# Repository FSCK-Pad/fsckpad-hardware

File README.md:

# FSCKPad Hardware

## Openhardware game controller/emulation handheld

---

## Installation

`cd fsckpad-hardware`  
`make install-dev`  

## Usage

`$ make help`  
`$ make build`  

---
Created from device-cookiecutter, https://github.com/crashfrog/device-cookiecutter

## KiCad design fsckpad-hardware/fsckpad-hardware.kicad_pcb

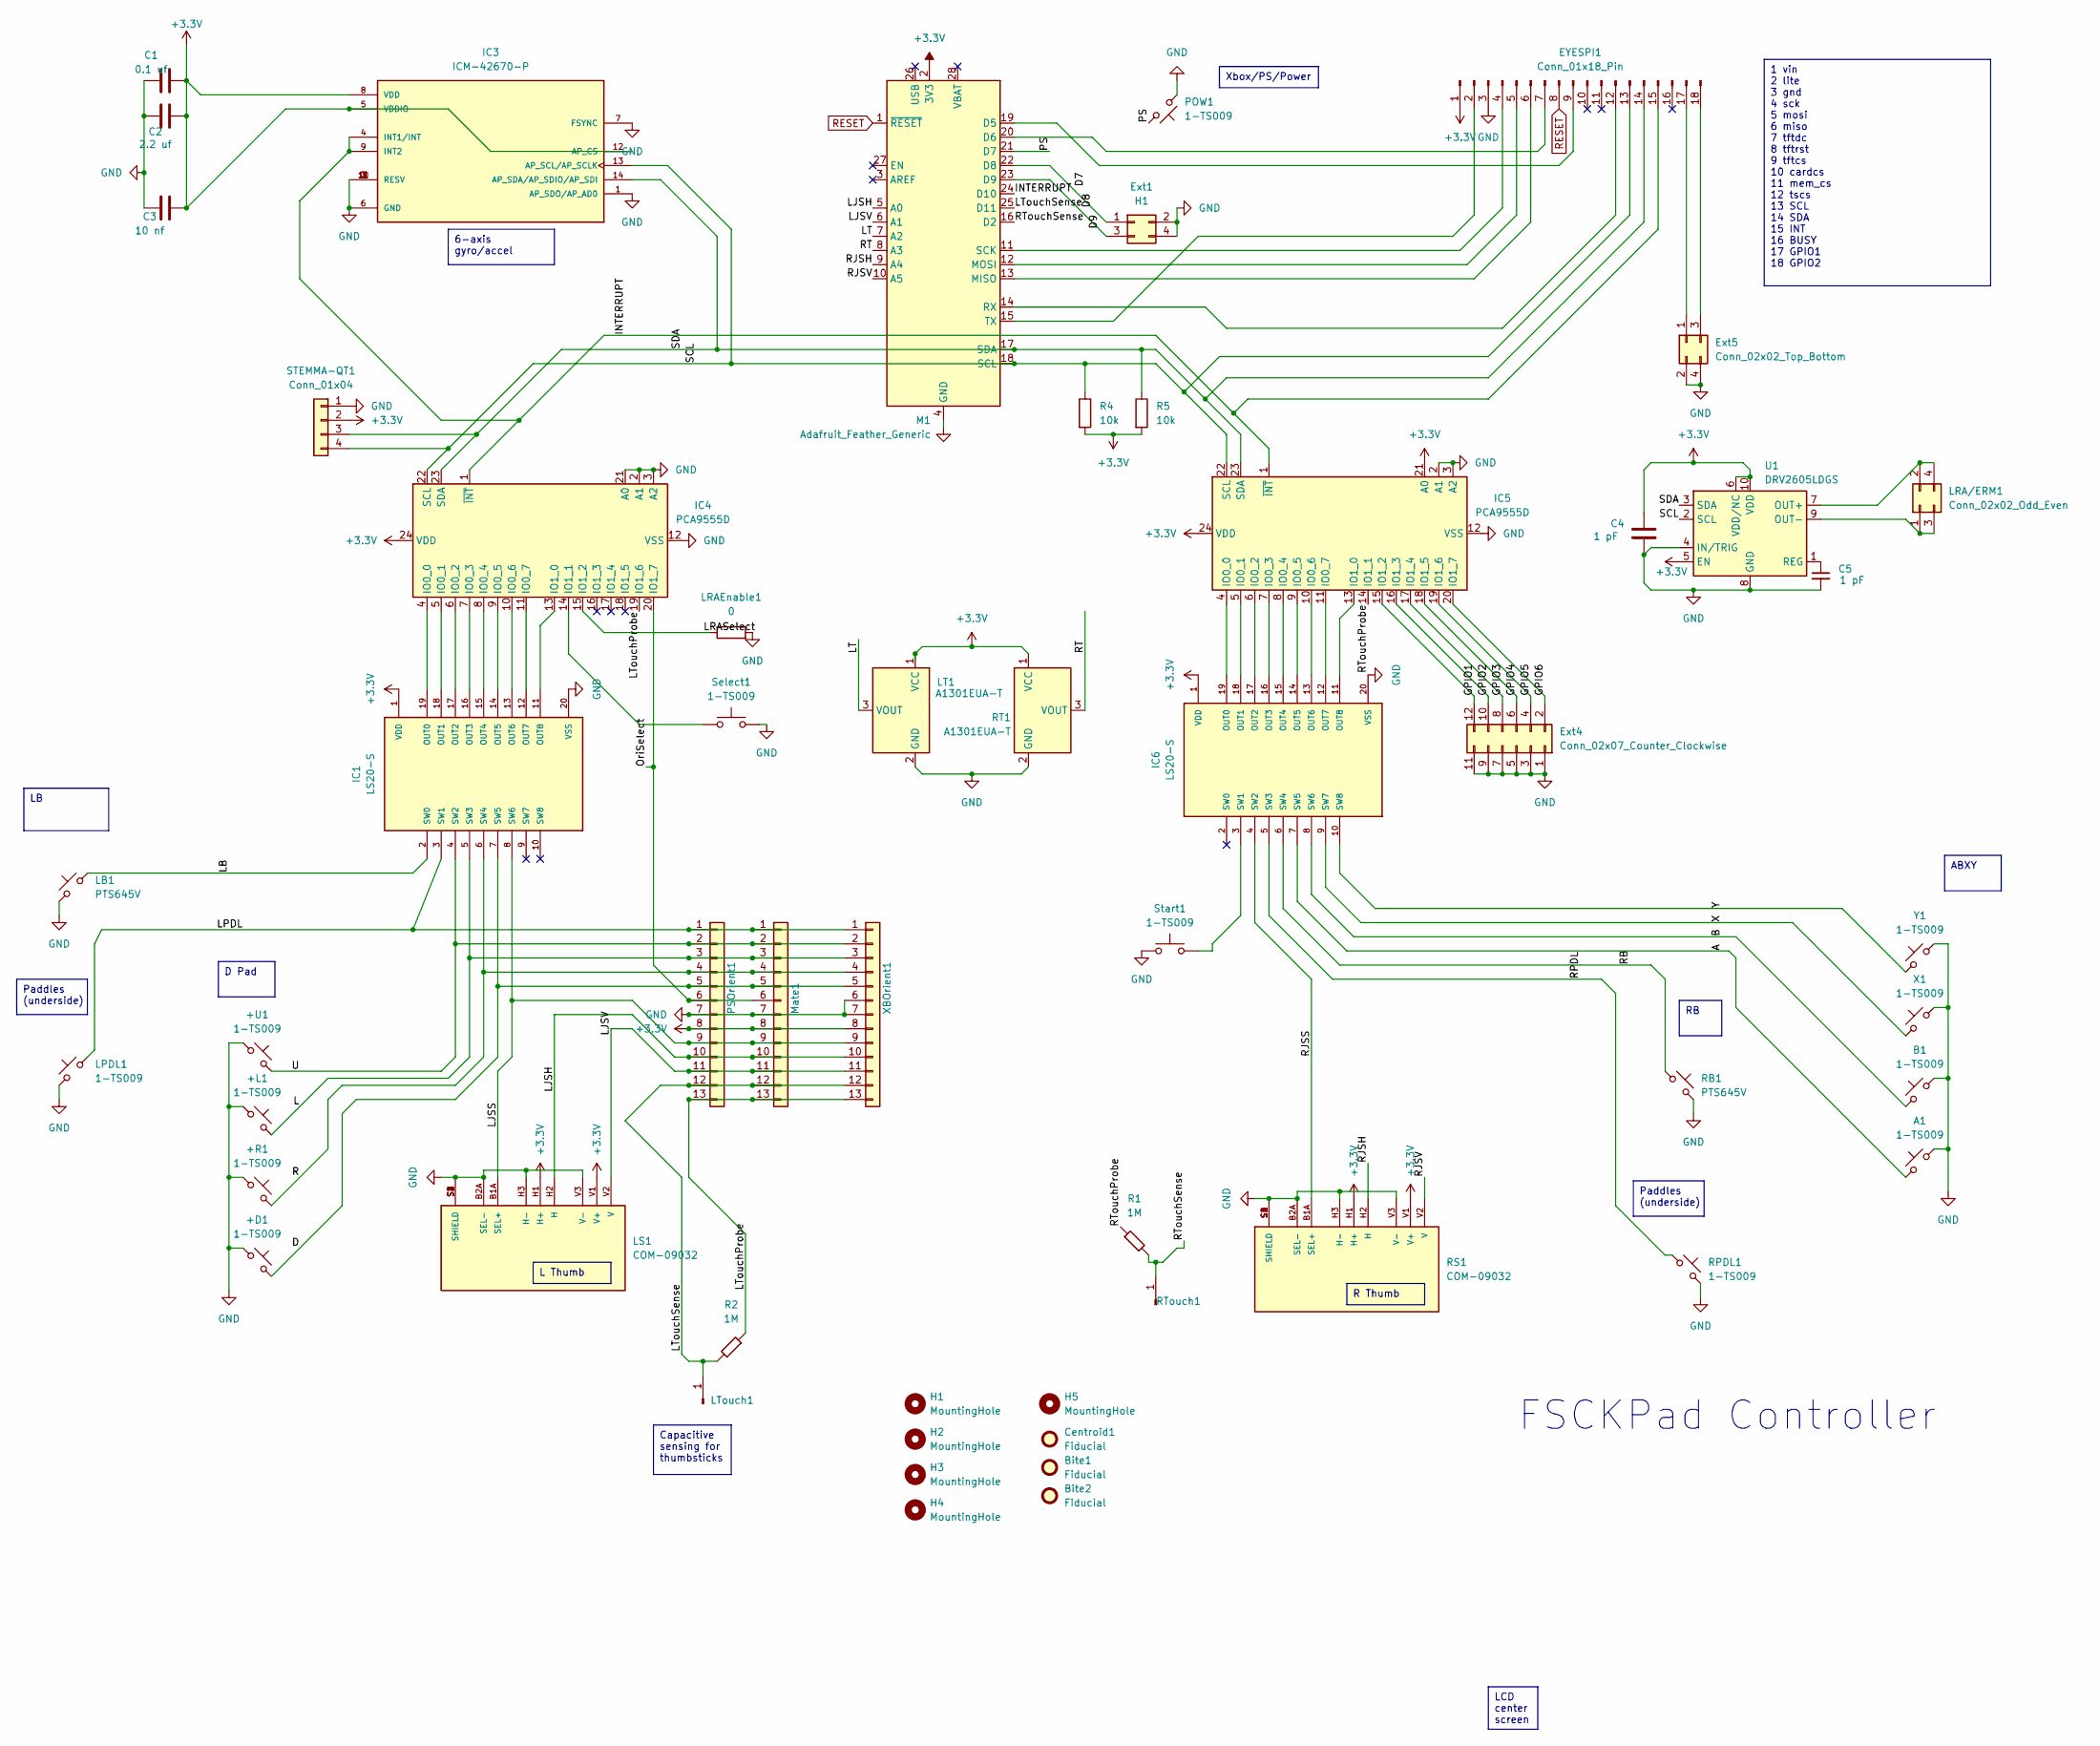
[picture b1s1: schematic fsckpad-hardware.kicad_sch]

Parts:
+D1: 1-TS009; SW_Push_1TS009_Conductive_Pad
+L1: 1-TS009; SW_Push_1TS009_Conductive_Pad
+R1: 1-TS009; SW_Push_1TS009_Conductive_Pad
+U1: 1-TS009; SW_Push_1TS009_Conductive_Pad
A1: 1-TS009; SW_Push_1TS009_Conductive_Pad
B1: 1-TS009; SW_Push_1TS009_Conductive_Pad
Bite1, Bite2: Fiducial; 6.5mm_MouseBite
C1: 0.1 uf; C_0603_1608Metric_Pad1.08x0.95mm_HandSolder
C2: 2.2 uf; C_0603_1608Metric_Pad1.08x0.95mm_HandSolder
C3: 10 nf; C_0603_1608Metric_Pad1.08x0.95mm_HandSolder
C4, C5: 1 pF; C_0603_1608Metric_Pad1.08x0.95mm_HandSolder
Centroid1: Fiducial; OSHW-Logo2_7.3x6mm_SilkScreen
EYESPI1: Conn_01x18_Pin; Hirose_FH12-18S-0.5SH_1x18-1MP_P0.50mm_Horizontal
Ext1: H1; PinHeader_2x02_P1.00mm_Vertical
Ext4: Conn_02x07_Counter_Clockwise; PinHeader_2x06_P1.00mm_Vertical
Ext5: Conn_02x02_Top_Bottom; PinHeader_2x02_P1.00mm_Vertical
H1, H2, H3, H4, H5: MountingHole; MountingHole_2.7mm_M2.5_DIN965
IC1, IC6: LS20-S; SOIC-20_W7.5mm; PARTREV March 2023
IC3: ICM-42670-P; XDCR_ICM-42670-P; PARTREV 1.1
IC4, IC5: PCA9555D; SOIC-24W_7.5x15.4mm_P1.27mm
LB1: PTS645V; SW_Tactile_SPST_Angled_PTS645Vx39-2LFS
LPDL1: 1-TS009; SW_Push_1P1T_NO_6x6mm_H9.5mm
LRA/ERM1: Conn_02x02_Odd_Even; PinHeader_2x02_P1.00mm_Vertical
LRAEnable1: 0; SolderJumper-2_P1.3mm_Open_TrianglePad1.0x1.5mm
LS1: COM-09032; XDCR_COM-09032; PARTREV N/A
LT1: A1301EUA-T; TO-92Flat
LTouch1: Conn_01x01_Pin; PinHeader_1x01_P1.00mm_Vertical
M1: Adafruit_Feather_Generic; Adafruit_Feather
Mate1: Conn_01x13; BridgeableComb_1x13_Reverse
POW1: 1-TS009; SW_Push_1TS009_Conductive_Pad
PSOrient1: Conn_01x13; BridgeableComb_1x13
R1, R2: 1M; R_0603_1608Metric_Pad0.98x0.95mm_HandSolder
R4, R5: 10k; R_0603_1608Metric_Pad0.98x0.95mm_HandSolder
RB1: PTS645V; SW_Tactile_SPST_Angled_PTS645Vx39-2LFS
RPDL1: 1-TS009; SW_Push_1P1T_NO_6x6mm_H9.5mm
RS1: COM-09032; XDCR_COM-09032; PARTREV N/A
RT1: A1301EUA-T; TO-92Flat
RTouch1: Conn_01x01_Pin; PinHeader_1x01_P1.00mm_Vertical
STEMMA-QT1: Conn_01x04; JST_SH_SM04B-SRSS-TB_1x04-1MP_P1.00mm_Horizontal
Select1: 1-TS009; SW_Push_1TS009_Conductive_Pad
Start1: 1-TS009; SW_Push_1TS009_Conductive_Pad
U1: DRV2605LDGS; VSSOP-10_3x3mm_P0.5mm
X1: 1-TS009; SW_Push_1TS009_Conductive_Pad
XBOrient1: Conn_01x13; BridgeableComb_1x13
Y1: 1-TS009; SW_Push_1TS009_Conductive_Pad

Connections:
+3.3V: C1.2, C2.2, C3.2, C4.1, EYESPI1.1, IC1.1 (VDD), IC3.5 (VDDIO), IC3.8 (VDD), IC3.12 (AP_CS), IC4.24 (VDD), IC5.21 (A0), IC5.24 (VDD), IC6.1 (VDD), LS1.H1 (H+), LS1.V1 (V+), LT1.1 (VCC), M1.2 (3V3), Mate1.8, PSOrient1.8, R4.2, R5.2, RS1.H1 (H+), RS1.V1 (V+), RT1.1 (VCC), STEMMA-QT1.2, U1.5 (EN), U1.6 (VDD/NC), U1.10 (VDD), U1.H1, U1.V1, XBOrient1.8; also elsewhere on the board
/A: A1.2, IC6.7 (SW5)
/B: B1.2, IC6.8 (SW6)
/D: +D1.2, IC1.7 (SW5), Mate1.5, PSOrient1.5, XBOrient1.5; also elsewhere on the board
/D8: Ext1.1, M1.22 (D8); also elsewhere on the board
/D9: Ext1.3, M1.23 (D9); also elsewhere on the board
/GPIO1: Ext4.12, IC5.15 (IO1_2)
/GPIO2: Ext4.10, IC5.16 (IO1_3)
/GPIO3: Ext4.8, IC5.17 (IO1_4)
/GPIO4: Ext4.6, IC5.18 (IO1_5)
/GPIO5: Ext4.4, IC5.19 (IO1_6)
/GPIO6: Ext4.2, IC5.20 (IO1_7)
/INTERRUPT: EYESPI1.15, IC3.4 (INT1/INT), IC3.9 (INT2), IC4.1 (~INT), IC5.1 (~INT), M1.24 (D10); also elsewhere on the board
/L: +L1.2, IC1.5 (SW3), Mate1.3, PSOrient1.3, XBOrient1.3; also elsewhere on the board
/LB: IC1.2 (SW0), LB1.2
/LJSH: LS1.H2 (H), M1.5 (A0), Mate1.10, PSOrient1.10, U1.H2, XBOrient1.10; also elsewhere on the board
/LJSS: IC1.8 (SW6), LS1.B1A (SEL+), Mate1.9, PSOrient1.9, U1.B1A, XBOrient1.9; also elsewhere on the board
/LJSV: LS1.V2 (V), M1.6 (A1), Mate1.11, PSOrient1.11, U1.V2, XBOrient1.11; also elsewhere on the board
/LPDL: IC1.3 (SW1), LPDL1.2, Mate1.1, PSOrient1.1, XBOrient1.1; also elsewhere on the board
/LRASelect: IC4.15 (IO1_2), LRAEnable1.1; also elsewhere on the board
/LT: LT1.3 (VOUT), M1.7 (A2); also elsewhere on the board
/LTouchProbe: IC4.19 (IO1_6), Mate1.13, PSOrient1.13, R2.1, XBOrient1.13; also elsewhere on the board
/LTouchSense: LTouch1.1, M1.25 (D11), Mate1.12, PSOrient1.12, R2.2, XBOrient1.12; also elsewhere on the board
/OriSelect: IC4.20 (IO1_7), Mate1.6, PSOrient1.6; also elsewhere on the board
/PS: M1.21 (D7), POW1.2; also elsewhere on the board
/R: +R1.2, IC1.6 (SW4), Mate1.4, PSOrient1.4, XBOrient1.4; also elsewhere on the board
/RB: IC6.6 (SW4), RB1.2
/RJSH: M1.9 (A4), RS1.H2 (H); also elsewhere on the board
/RJSS: IC6.4 (SW2), RS1.B1A (SEL+)
/RJSV: M1.10 (A5), RS1.V2 (V); also elsewhere on the board
/RPDL: IC6.5 (SW3), RPDL1.2
/RT: M1.8 (A3), RT1.3 (VOUT); also elsewhere on the board
/RTouchProbe: IC5.14 (IO1_1), R1.1
/RTouchSense: M1.16 (D2), R1.2, RTouch1.1; also elsewhere on the board
/SCL: EYESPI1.13, IC3.13 (AP_SCL/AP_SCLK), IC4.22 (SCL), IC5.22 (SCL), M1.18 (SCL), R4.1, STEMMA-QT1.4, U1.2 (SCL); also elsewhere on the board
/SDA: EYESPI1.14, IC3.14 (AP_SDA/AP_SDIO/AP_SDI), IC4.23 (SDA), IC5.23 (SDA), M1.17 (SDA), R5.1, STEMMA-QT1.3, U1.3 (SDA); also elsewhere on the board
/U: +U1.2, IC1.4 (SW2), Mate1.2, PSOrient1.2, XBOrient1.2; also elsewhere on the board
/X: IC6.9 (SW7), X1.2
/Y: IC6.10 (SW8), Y1.2
GND: +D1.1, +L1.1, +R1.1, +U1.1, A1.1, B1.1, C1.1, C2.1, C3.1, C4.2, C5.2, EYESPI1.3, Ext1.2, Ext1.4, Ext4.1, Ext4.3, Ext4.5, Ext4.7, Ext4.9, Ext4.11, Ext5.2, Ext5.4, IC1.20 (VSS), IC3.1 (AP_SDO/AP_AD0), IC3.2 (RESV), IC3.3 (RESV), IC3.6 (GND), IC3.7 (FSYNC), IC3.10 (RESV), IC3.11 (RESV), IC4.2 (A1), IC4.3 (A2), IC4.12 (VSS), IC4.21 (A0), IC5.2 (A1), IC5.3 (A2), IC5.12 (VSS), IC6.20 (VSS), LB1.1, LPDL1.1, LRAEnable1.2, LS1.B2A (SEL-), LS1.H3 (H-), LS1.S1 (SHIELD), LS1.S2 (SHIELD), LS1.S3 (SHIELD), LS1.S4 (SHIELD), LS1.V3 (V-), LT1.2 (GND), M1.4 (GND), Mate1.7, POW1.1, PSOrient1.7, RB1.1, RPDL1.1, RS1.B2A (SEL-), RS1.H3 (H-), RS1.S1 (SHIELD), RS1.S2 (SHIELD), RS1.S3 (SHIELD), RS1.S4 (SHIELD), RS1.V3 (V-), RT1.2 (GND), STEMMA-QT1.1, Select1.2, Start1.2, U1.4 (IN/TRIG), U1.8 (GND), U1.B2A, U1.H3, U1.S1, U1.S2, U1.S3, U1.S4, U1.V3, X1.1, XBOrient1.6, XBOrient1.7, Y1.1; also elsewhere on the board
unnamed 40: EYESPI1.2, M1.15 (TX); also elsewhere on the board
unnamed 41: EYESPI1.4, M1.11 (SCK); also elsewhere on the board
unnamed 42: EYESPI1.5, M1.12 (MOSI); also elsewhere on the board
unnamed 43: EYESPI1.6, M1.13 (MISO); also elsewhere on the board
unnamed 44: EYESPI1.7, M1.20 (D6); also elsewhere on the board
unnamed 45: EYESPI1.9, M1.19 (D5); also elsewhere on the board
unnamed 46: EYESPI1.12, M1.14 (RX); also elsewhere on the board
unnamed: EYESPI1.17, Ext5.1
unnamed: EYESPI1.18, Ext5.3
unnamed: IC1.19 (OUT0), IC4.4 (IO0_0)
unnamed: IC1.18 (OUT1), IC4.5 (IO0_1)
unnamed: IC1.17 (OUT2), IC4.6 (IO0_2)
unnamed: IC1.16 (OUT3), IC4.7 (IO0_3)
unnamed: IC1.15 (OUT4), IC4.8 (IO0_4)
unnamed: IC1.14 (OUT5), IC4.9 (IO0_5)
unnamed: IC1.13 (OUT6), IC4.10 (IO0_6)
unnamed: IC1.12 (OUT7), IC4.11 (IO0_7)
unnamed: IC1.11 (OUT8), IC4.13 (IO1_0)
unnamed: IC4.14 (IO1_1), Select1.1
unnamed: IC5.4 (IO0_0), IC6.19 (OUT0)
unnamed: IC5.5 (IO0_1), IC6.18 (OUT1)
unnamed: IC5.6 (IO0_2), IC6.17 (OUT2)
unnamed: IC5.7 (IO0_3), IC6.16 (OUT3)
unnamed: IC5.8 (IO0_4), IC6.15 (OUT4)
unnamed: IC5.9 (IO0_5), IC6.14 (OUT5)
unnamed: IC5.10 (IO0_6), IC6.13 (OUT6)
unnamed: IC5.11 (IO0_7), IC6.12 (OUT7)
unnamed: IC5.13 (IO1_0), IC6.11 (OUT8)
unnamed: IC6.3 (SW1), Start1.1
unnamed: LRA/ERM1.1, LRA/ERM1.3, U1.9 (OUT-)
unnamed: LRA/ERM1.2, LRA/ERM1.4, U1.7 (OUT+)
unnamed: C5.1, U1.1 (REG)
RESET: EYESPI1.8, M1.1 (~RESET); also elsewhere on the board

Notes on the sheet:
Capacitive sensing for thumbsticks
1 vin 2 lite 3 gnd 4 sck 5 mosi 6 miso 7 tftdc 8 tftrst 9 tftcs 10 cardcs 11 mem_cs 12 tscs 13 SCL 14 SDA 15 INT 16 BUSY 17 GPIO1 18 GPIO2
R Thumb
6-axis gyro/accel
L Thumb
Xbox/PS/Power
Paddles (underside)
ABXY
D Pad
LCD center screen
FSCKPad Controller

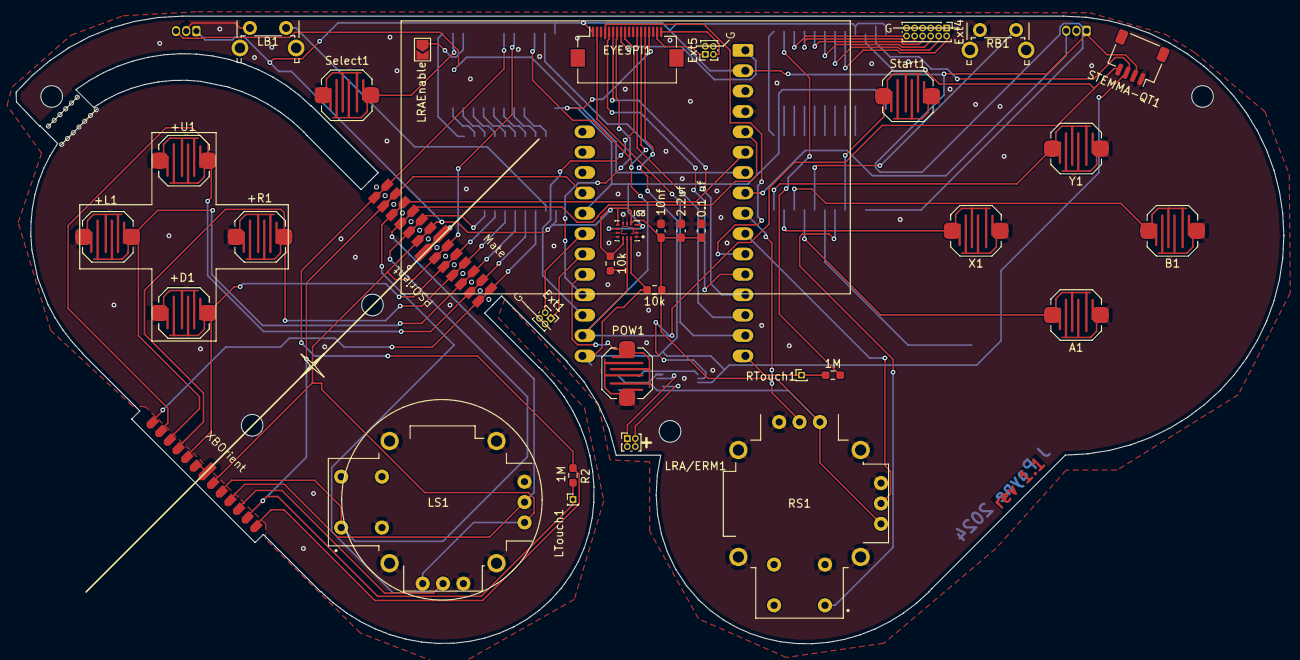
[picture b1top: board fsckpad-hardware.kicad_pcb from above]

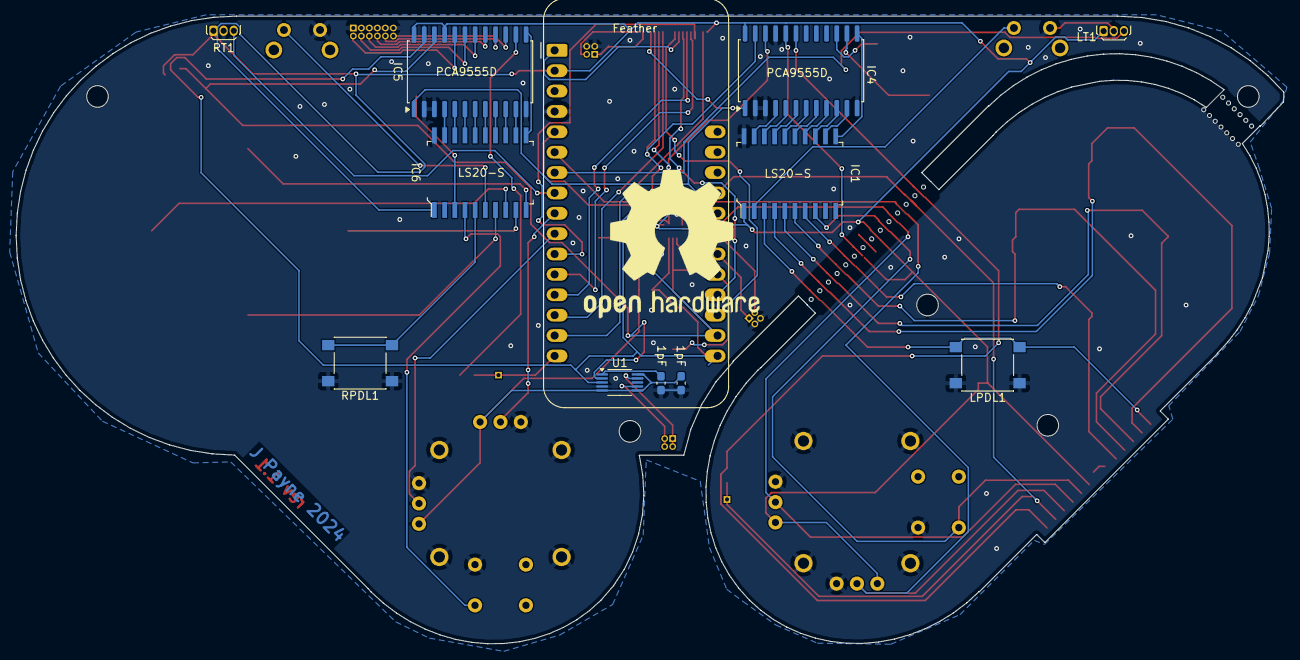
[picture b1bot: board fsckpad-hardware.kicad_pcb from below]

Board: 2 copper layers, 158.1 x 78.3 mm, 55 parts (13 on the bottom side), 73 nets.

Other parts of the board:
Feather: Adafruit_Feather_Generic; Adafruit_Feather
LRAEnable: 0; SolderJumper-2_P1.3mm_Open_TrianglePad1.0x1.5mm
Mate: Conn_01x13; BridgeableComb_1x13_Reverse
PSOrient: Conn_01x13; BridgeableComb_1x13
XBOrient: Conn_01x13; BridgeableComb_1x13

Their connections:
+3.3V: Feather.2 (3V3), Mate.8, PSOrient.8, XBOrient.8; also elsewhere on the board
/D: Mate.5, PSOrient.5, XBOrient.5; also elsewhere on the board
/D8: Feather.22 (D8); also elsewhere on the board
/D9: Feather.23 (D9); also elsewhere on the board
/INTERRUPT: Feather.24 (D10); also elsewhere on the board
/L: Mate.3, PSOrient.3, XBOrient.3; also elsewhere on the board
/LJSH: Feather.5 (A0), Mate.10, PSOrient.10, XBOrient.10; also elsewhere on the board
/LJSS: Mate.9, PSOrient.9, XBOrient.9; also elsewhere on the board
/LJSV: Feather.6 (A1), Mate.11, PSOrient.11, XBOrient.11; also elsewhere on the board
/LPDL: Mate.1, PSOrient.1, XBOrient.1; also elsewhere on the board
/LRASelect: LRAEnable.1; also elsewhere on the board
/LT: Feather.7 (A2); also elsewhere on the board
/LTouchProbe: Mate.13, PSOrient.13, XBOrient.13; also elsewhere on the board
/LTouchSense: Feather.25 (D11), Mate.12, PSOrient.12, XBOrient.12; also elsewhere on the board
/OriSelect: Mate.6, PSOrient.6; also elsewhere on the board
/PS: Feather.21 (D7); also elsewhere on the board
/R: Mate.4, PSOrient.4, XBOrient.4; also elsewhere on the board
/RJSH: Feather.9 (A4); also elsewhere on the board
/RJSV: Feather.10 (A5); also elsewhere on the board
/RT: Feather.8 (A3); also elsewhere on the board
/RTouchSense: Feather.16 (D2); also elsewhere on the board
/SCL: Feather.18 (SCL); also elsewhere on the board
/SDA: Feather.17 (SDA); also elsewhere on the board
/U: Mate.2, PSOrient.2, XBOrient.2; also elsewhere on the board
GND: Feather.4 (GND), LRAEnable.2, Mate.7, PSOrient.7, XBOrient.6, XBOrient.7; also elsewhere on the board
unnamed 40: Feather.15 (TX); also elsewhere on the board
unnamed 41: Feather.11 (SCK); also elsewhere on the board
unnamed 42: Feather.12 (MOSI); also elsewhere on the board
unnamed 43: Feather.13 (MISO); also elsewhere on the board
unnamed 44: Feather.20 (D6); also elsewhere on the board
unnamed 45: Feather.19 (D5); also elsewhere on the board
unnamed 46: Feather.14 (RX); also elsewhere on the board
RESET: Feather.1 (~RESET); also elsewhere on the board

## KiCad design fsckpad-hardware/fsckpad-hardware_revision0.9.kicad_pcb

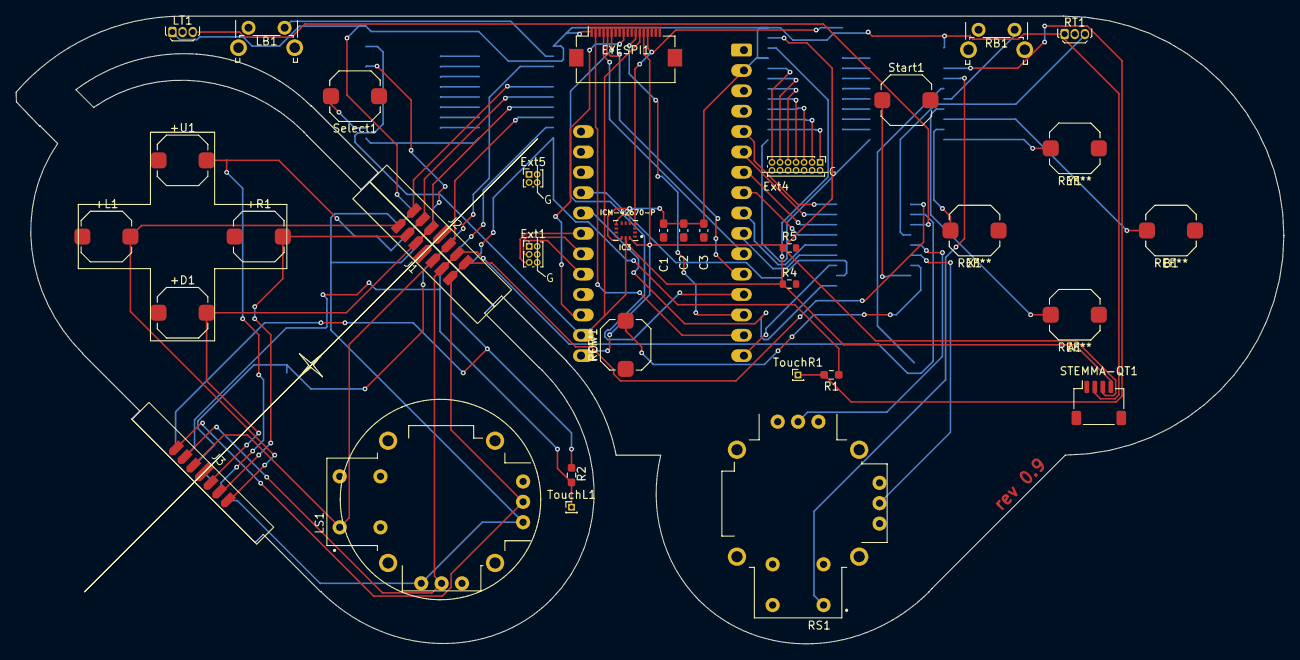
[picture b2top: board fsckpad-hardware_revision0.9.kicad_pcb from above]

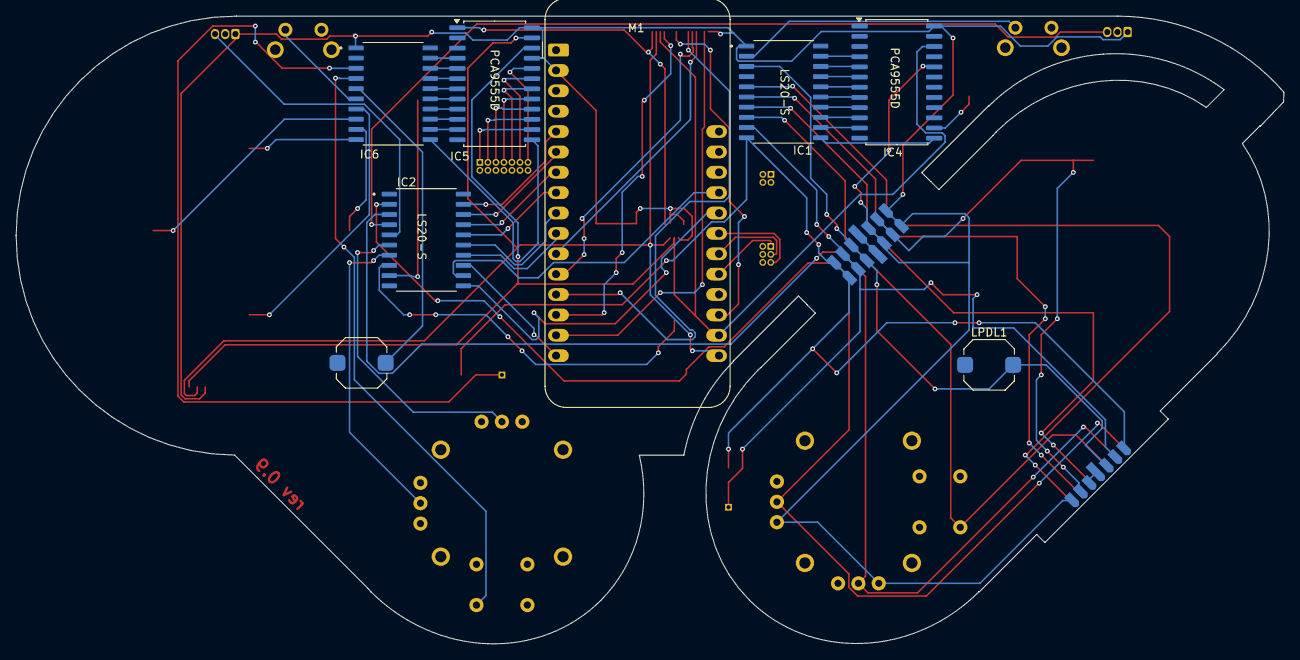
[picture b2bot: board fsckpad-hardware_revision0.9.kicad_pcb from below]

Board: 2 copper layers, 158.1 x 78.3 mm, 43 parts (8 on the bottom side), 78 nets.

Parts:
+D1: 1-TS009; SW_Push_1TS009xxxx-xxxx-xxxx_6x6x5mm
+L1: 1-TS009; SW_Push_1TS009xxxx-xxxx-xxxx_6x6x5mm
+R1: 1-TS009; SW_Push_1TS009xxxx-xxxx-xxxx_6x6x5mm
+U1: 1-TS009; SW_Push_1TS009xxxx-xxxx-xxxx_6x6x5mm
A1: 1-TS009; SW_Push_1TS009xxxx-xxxx-xxxx_6x6x5mm
B1: 1-TS009; SW_Push_1TS009xxxx-xxxx-xxxx_6x6x5mm
C1: 0.1 uf; C_0603_1608Metric_Pad1.08x0.95mm_HandSolder
C2: 2.2 uf; C_0603_1608Metric_Pad1.08x0.95mm_HandSolder
C3: 10 nf; C_0603_1608Metric_Pad1.08x0.95mm_HandSolder
EYESPI1: Conn_01x18_Pin; Hirose_FH12-18S-0.5SH_1x18-1MP_P0.50mm_Horizontal
Ext1: H1; PinHeader_2x03_P1.00mm_Vertical
Ext4: Conn_02x07_Counter_Clockwise; PinHeader_2x07_P1.00mm_Vertical
Ext5: Conn_02x02_Top_Bottom; PinHeader_2x02_P1.00mm_Vertical
IC1, IC2, IC6: LS20-S; SOIC127P1033X265-20N
IC3: ICM-42670-P; XDCR_ICM-42670-P
IC4, IC5: PCA9555D; SOIC-24W_7.5x15.4mm_P1.27mm
J1: PS Orient; BridgeableComb_2x7
J2: Mate; BridgeableComb_2x7
J3: Xbox Orient; BridgeableComb_2x7
LB1: PTS645V; SW_Tactile_SPST_Angled_PTS645Vx39-2LFS
LPDL1: 1-TS009; SW_Push_1TS009xxxx-xxxx-xxxx_6x6x5mm
LS1: COM-09032; XDCR_COM-09032
LT1: A1301EUA-T; TO-92Flat
M1: Adafruit_Feather_Generic; Adafruit_Feather
POW1: SW; SW_Push_1TS009xxxx-xxxx-xxxx_6x6x5mm
R1, R2: 1M; R_0603_1608Metric_Pad0.98x0.95mm_HandSolder
R4, R5: 10k; R_0603_1608Metric
RB1: PTS645V; SW_Tactile_SPST_Angled_PTS645Vx39-2LFS
RPDL1: 1-TS009; SW_Push_1TS009xxxx-xxxx-xxxx_6x6x5mm
RS1: COM-09032; XDCR_COM-09032
RT1: A1301EUA-T; TO-92Flat
STEMMA-QT1: Conn_01x04; JST_SH_SM04B-SRSS-TB_1x04-1MP_P1.00mm_Horizontal
Select1: 1-TS009; SW_Push_1TS009xxxx-xxxx-xxxx_6x6x5mm
Start1: 1-TS009; SW_Push_1TS009xxxx-xxxx-xxxx_6x6x5mm
TouchL1: Touch L; PinHeader_1x01_P1.00mm_Vertical
TouchR1: Touch R; PinHeader_1x01_P1.00mm_Vertical
X1: 1-TS009; SW_Push_1TS009xxxx-xxxx-xxxx_6x6x5mm
Y1: 1-TS009; SW_Push_1TS009xxxx-xxxx-xxxx_6x6x5mm

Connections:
+3.3V: C1.2, C2.2, C3.2, EYESPI1.1, IC1.1 (VDD), IC2.1 (VDD), IC3.5 (VDDIO), IC3.8 (VDD), IC3.12 (AP_CS), IC4.24 (VDD), IC5.21 (A0), IC5.24 (VDD), IC6.1 (VDD), J1.14, J2.14, J3.14, LS1.H1 (H+), LS1.V1 (V+), LT1.1 (VCC), M1.2 (3V3), R4.2, R5.2, RS1.H1 (H+), RS1.V1 (V+), RT1.1 (VCC), STEMMA-QT1.2
/A: A1.2, IC6.7 (SW5)
/A0: IC2.19 (OUT0), M1.5 (A0)
/A1: IC2.18 (OUT1), M1.6 (A1)
/A2: IC2.17 (OUT2), M1.7 (A2)
/A3: IC2.16 (OUT3), M1.8 (A3)
/A4: IC2.15 (OUT4), M1.9 (A4)
/A5: IC2.14 (OUT5), M1.10 (A5)
/B: B1.2, IC6.8 (SW6)
/D: +D1.2, IC1.7 (SW5), J1.5, J2.5, J3.5
/D7: Ext1.1, M1.21 (D7)
/D8: Ext1.3, M1.22 (D8)
/D9: Ext1.5, M1.23 (D9)
/GPIO1: Ext4.1, IC5.14 (IO1_1)
/GPIO2: Ext4.3, IC5.15 (IO1_2)
/GPIO3: Ext4.5, IC5.16 (IO1_3)
/GPIO4: Ext4.7, IC5.17 (IO1_4)
/GPIO5: Ext4.9, IC5.18 (IO1_5)
/GPIO6: Ext4.11, IC5.19 (IO1_6)
/GPIO7: Ext4.13, IC5.20 (IO1_7)
/INTERRUPT: EYESPI1.15, IC3.4 (INT1/INT), IC3.9 (INT2), IC4.1 (~INT), IC5.1 (~INT)
/L: +L1.2, IC1.5 (SW3), J1.7, J2.7, J3.7
/LB: IC1.2 (SW0), LB1.2
/LJSH: IC2.2 (SW0), J1.1, J2.1, J3.1, LS1.H2 (H)
/LJSS: IC1.8 (SW6), J1.3, J2.3, J3.3, LS1.B1A (SEL+)
/LJSV: IC2.3 (SW1), J1.2, J2.2, J3.2, LS1.V2 (V)
/LPDL: IC1.3 (SW1), J1.10, J2.10, J3.10, LPDL1.2
/LT: IC2.4 (SW2), LT1.3 (VOUT)
/LTouchSense: IC1.9 (SW7), J1.9, J2.9, J3.9, R2.2
/PS: IC2.13 (OUT6), M1.16 (D2)
/R: +R1.2, IC1.6 (SW4), J1.6, J2.6, J3.6
/RB: IC6.6 (SW4), RB1.2
/RJSH: IC2.6 (SW4), RS1.H2 (H)
/RJSS: IC6.4 (SW2), RS1.B1A (SEL+)
/RJSV: IC2.7 (SW5), RS1.V2 (V)
/RPDL: IC6.5 (SW3), RPDL1.2
/RT: IC2.5 (SW3), RT1.3 (VOUT)
/RTouchSense: IC6.3 (SW1), R1.2
/SCL: EYESPI1.13, IC3.13 (AP_SCL/AP_SCLK), IC4.22 (SCL), IC5.22 (SCL), M1.18 (SCL), R4.1, STEMMA-QT1.4
/SDA: EYESPI1.14, IC3.14 (AP_SDA/AP_SDIO/AP_SDI), IC4.23 (SDA), IC5.23 (SDA), M1.17 (SDA), R5.1, STEMMA-QT1.3
/START: IC2.12 (OUT7), M1.25 (D11)
/TouchProbe: IC1.10 (SW8), J1.8, J2.8, J3.8, R1.1, R2.1
/U: +U1.2, IC1.4 (SW2), J1.13, J2.13, J3.13
/X: IC6.9 (SW7), X1.2
/Y: IC6.10 (SW8), Y1.2
GND: +D1.1, +L1.1, +R1.1, +U1.1, A1.1, B1.1, C1.1, C2.1, C3.1, EYESPI1.3, Ext1.2, Ext1.4, Ext1.6, Ext4.2, Ext4.4, Ext4.6, Ext4.8, Ext4.10, Ext4.12, Ext4.14, Ext5.2, Ext5.4, IC1.20 (VSS), IC2.20 (VSS), IC3.1 (AP_SDO/AP_AD0), IC3.2 (RESV), IC3.3 (RESV), IC3.6 (GND), IC3.7 (FSYNC), IC3.10 (RESV), IC3.11 (RESV), IC4.2 (A1), IC4.3 (A2), IC4.12 (VSS), IC4.21 (A0), IC5.2 (A1), IC5.3 (A2), IC5.12 (VSS), IC6.2 (SW0), IC6.20 (VSS), J1.4, J1.11, J2.4, J2.11, J3.4, J3.11, J3.12, LB1.1, LPDL1.1, LS1.B2A (SEL-), LS1.H3 (H-), LS1.S1 (SHIELD), LS1.S2 (SHIELD), LS1.S3 (SHIELD), LS1.S4 (SHIELD), LS1.V3 (V-), LT1.2 (GND), M1.4 (GND), POW1.1, RB1.1, RPDL1.1, RS1.B2A (SEL-), RS1.H3 (H-), RS1.S1 (SHIELD), RS1.S2 (SHIELD), RS1.S3 (SHIELD), RS1.S4 (SHIELD), RS1.V3 (V-), RT1.2 (GND), STEMMA-QT1.1, Select1.2, Start1.2, X1.1, Y1.1
unnamed: EYESPI1.2, M1.15 (TX)
unnamed: EYESPI1.4, M1.11 (SCK)
unnamed: EYESPI1.5, M1.12 (MOSI)
unnamed: EYESPI1.6, M1.13 (MISO)
unnamed: EYESPI1.7, M1.20 (D6)
unnamed: EYESPI1.9, M1.19 (D5)
unnamed: EYESPI1.12, M1.14 (RX)
unnamed: EYESPI1.17, Ext5.1
unnamed: EYESPI1.18, Ext5.3
unnamed: IC1.19 (OUT0), IC4.4 (IO0_0)
unnamed: IC1.18 (OUT1), IC4.5 (IO0_1)
unnamed: IC1.17 (OUT2), IC4.6 (IO0_2)
unnamed: IC1.16 (OUT3), IC4.7 (IO0_3)
unnamed: IC1.15 (OUT4), IC4.8 (IO0_4)
unnamed: IC1.14 (OUT5), IC4.9 (IO0_5)
unnamed: IC1.13 (OUT6), IC4.10 (IO0_6)
unnamed: IC1.12 (OUT7), IC4.11 (IO0_7)
unnamed: IC1.11 (OUT8), IC4.13 (IO1_0)
unnamed: IC2.8 (SW6), POW1.2
unnamed: IC2.9 (SW7), Start1.1
unnamed: IC4.14 (IO1_1), Select1.1
unnamed: IC5.4 (IO0_0), IC6.19 (OUT0)
unnamed: IC5.5 (IO0_1), IC6.18 (OUT1)
unnamed: IC5.6 (IO0_2), IC6.17 (OUT2)
unnamed: IC5.7 (IO0_3), IC6.16 (OUT3)
unnamed: IC5.8 (IO0_4), IC6.15 (OUT4)
unnamed: IC5.9 (IO0_5), IC6.14 (OUT5)
unnamed: IC5.10 (IO0_6), IC6.13 (OUT6)
unnamed: IC5.11 (IO0_7), IC6.12 (OUT7)
unnamed: IC5.13 (IO1_0), IC6.11 (OUT8)
Orientation_Select: IC4.20 (IO1_7), J1.12, J2.12
RESET: EYESPI1.8, M1.1 (~RESET)

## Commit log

2024-06-13 kicad autogen files
2024-06-13 initial schematics
2024-06-27 Revision 1.0 with haptic driver
2024-06-30 work
2024-06-30 readme
2024-06-30 starting enclosure, fixing board bugs
2024-07-04 rev 1
2024-07-11 revision 2, paramettric enclosure
2024-07-19 upper
